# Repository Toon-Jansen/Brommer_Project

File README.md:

# Brommer Alarm
### Door Lauren Debie en Toon Jansen
Dit project bestaat uit het maken van een brommer alarm dat het achterwiel van de brommer kan blokkeren en een sirenen kan laten afgaan wanneer deze op staat. Verder zal men het alarm kunne op en afzetten met zowel de brommer sleutel al een remote keycard.

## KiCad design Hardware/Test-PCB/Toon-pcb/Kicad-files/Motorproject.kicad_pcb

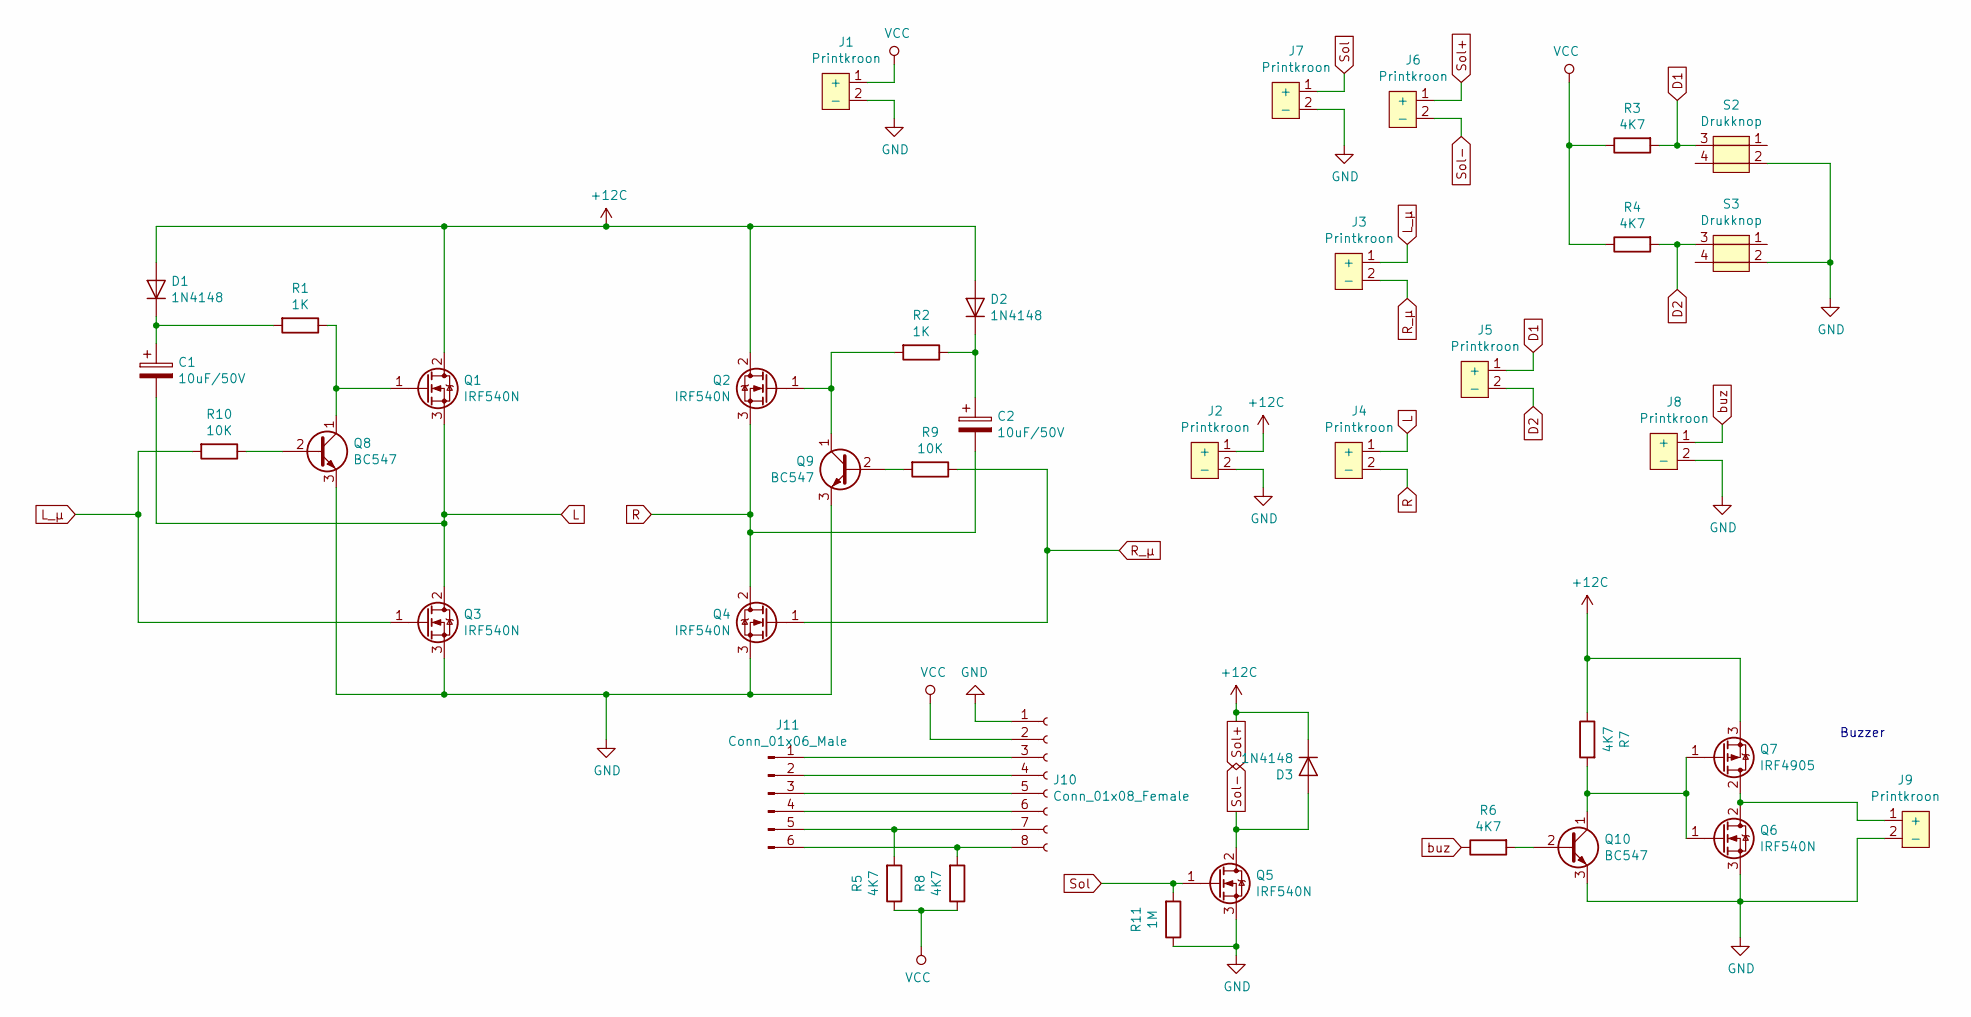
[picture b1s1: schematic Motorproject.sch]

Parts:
C1, C2: 10uF/50V; CP_EIA-6032-28_Kemet-C
D1, D2, D3: 1N4148; D_SOD-123
J1, J2, J3, J4, J5, J6, J7, J8, J9: Printkroon; SolderWirePad_1x02_P5.08mm_Drill1.5mm
J10: Conn_01x08_Female; PinHeader_1x08_P1.00mm_Vertical
J11: Conn_01x06_Male; PinHeader_1x06_P1.00mm_Vertical
Q1, Q2, Q3, Q4, Q5, Q6: IRF540N; TO-220-3_Vertical
Q7: IRF4905; TO-220-3_Vertical
Q8, Q9, Q10: BC547; TO-92_Inline
R1, R2: 1K; R_1206_3216Metric
R3, R4, R5, R6, R7, R8: 4K7; R_1206_3216Metric
R9, R10: 10K; R_1206_3216Metric
R11: 1M; R_1206_3216Metric
S2, S3: Drukknop; Drukknop_smd

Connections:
D1: J5.1 (+), R3.2, S2.3
D2: J5.2 (-), R4.2, S3.3
GND: J1.2 (-), J2.2 (-), J7.2 (-), J8.2 (-), J9.2 (-), J10.1, Q3.3 (S), Q4.3 (S), Q5.3 (S), Q6.3 (S), Q8.3 (E), Q9.3 (E), Q10.3 (E), R11.1, S2.2, S3.2
L: C1.2, J4.1 (+), Q1.3 (S), Q3.2 (D)
L_µ: J3.1 (+), Q3.1 (G), R10.2
unnamed: C1.1, D1.1 (K), R1.2
unnamed: C2.1, D2.1 (K), R2.1
unnamed: J9.1 (+), Q6.2 (D), Q7.2 (D)
unnamed: J10.3, J11.1
unnamed: J10.4, J11.2
unnamed: J10.5, J11.3
unnamed: J10.6, J11.4
unnamed: J10.7, J11.5, R5.2
unnamed: J10.8, J11.6, R8.2
unnamed: Q1.1 (G), Q8.1 (C), R1.1
unnamed: Q2.1 (G), Q9.1 (C), R2.2
unnamed: Q8.2 (B), R10.1
unnamed: Q9.2 (B), R9.2
unnamed: Q6.1 (G), Q7.1 (G), Q10.1 (C), R7.2
unnamed: Q10.2 (B), R6.2
R: C2.2, J4.2 (-), Q2.3 (S), Q4.2 (D)
R_µ: J3.2 (-), Q4.1 (G), R9.1
Sol: J7.1 (+), Q5.1 (G), R11.2
Sol+: D1.2 (A), D2.2 (A), D3.1 (K), J2.1 (+), J6.1 (+), Q1.2 (D), Q2.2 (D), Q7.3 (S), R7.1
Sol-: D3.2 (A), J6.2 (-), Q5.2 (D)
VCC: J1.1 (+), J10.2, R3.1, R4.1, R5.1, R8.1
buz: J8.1 (+), R6.1

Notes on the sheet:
Buzzer

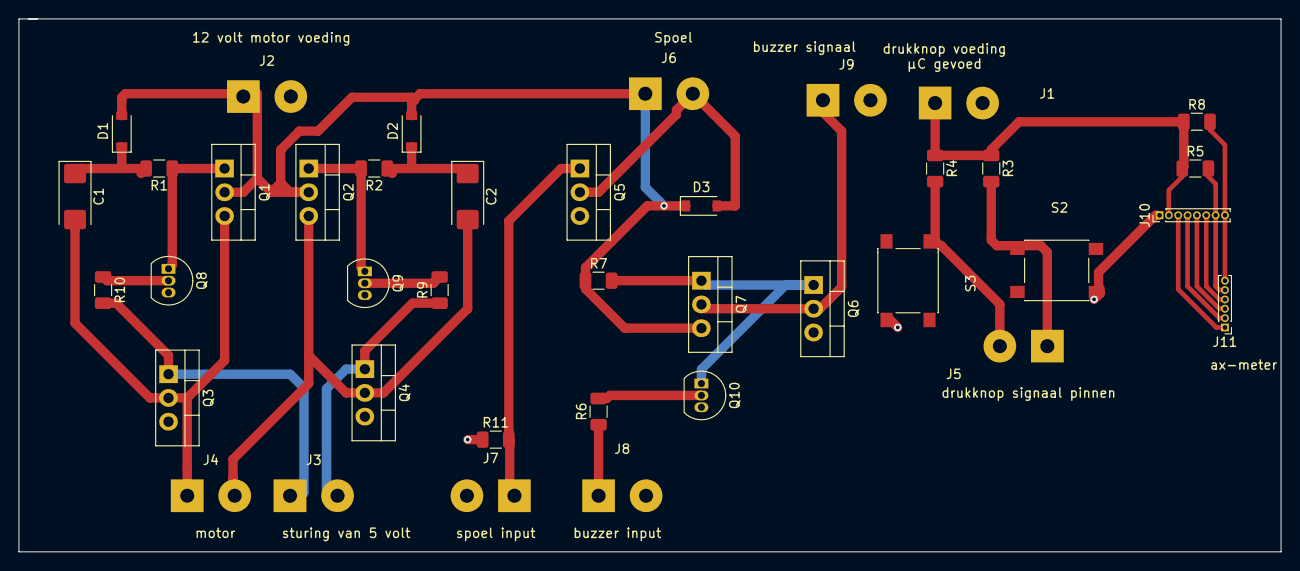
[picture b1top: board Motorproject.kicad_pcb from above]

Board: 2 copper layers, 135.0 x 57.0 mm, 39 parts (0 on the bottom side), 27 nets.

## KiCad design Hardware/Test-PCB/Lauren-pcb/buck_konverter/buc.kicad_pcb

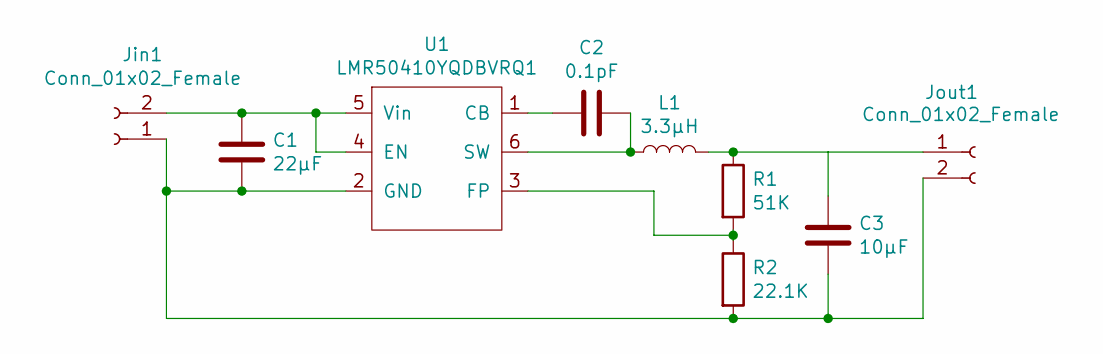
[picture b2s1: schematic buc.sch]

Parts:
C1: 22µF; C_0805_2012Metric
C2: 0.1pF; C_0805_2012Metric
C3: 10µF; C_0805_2012Metric
Jin1: Conn_01x02_Female; PinHeader_1x02_P2.54mm_Vertical
Jout1: Conn_01x02_Female; PinHeader_1x02_P2.54mm_Vertical
L1: 3.3µH; L_Taiyo-Yuden_MD-1616
R1: 51K; R_0603_1608Metric_Pad1.05x0.95mm_HandSolder
R2: 22.1K; R_0603_1608Metric_Pad1.05x0.95mm_HandSolder
U1: LMR50410YQDBVRQ1; SOT-23-6

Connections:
unnamed: C1.1, Jin1.2, U1.4 (EN), U1.5 (Vin)
unnamed: C1.2, C3.2, Jin1.1, Jout1.2, R2.2, U1.2 (GND)
unnamed: C2.1, U1.1 (CB)
unnamed: C2.2, L1.1, U1.6 (SW)
unnamed: C3.1, Jout1.1, L1.2, R1.1
unnamed: R1.2, R2.1, U1.3 (FP)

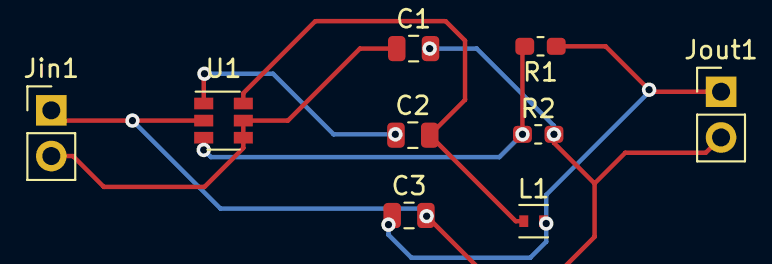
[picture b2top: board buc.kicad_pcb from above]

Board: 2 copper layers, 9 parts (0 on the bottom side), 6 nets.

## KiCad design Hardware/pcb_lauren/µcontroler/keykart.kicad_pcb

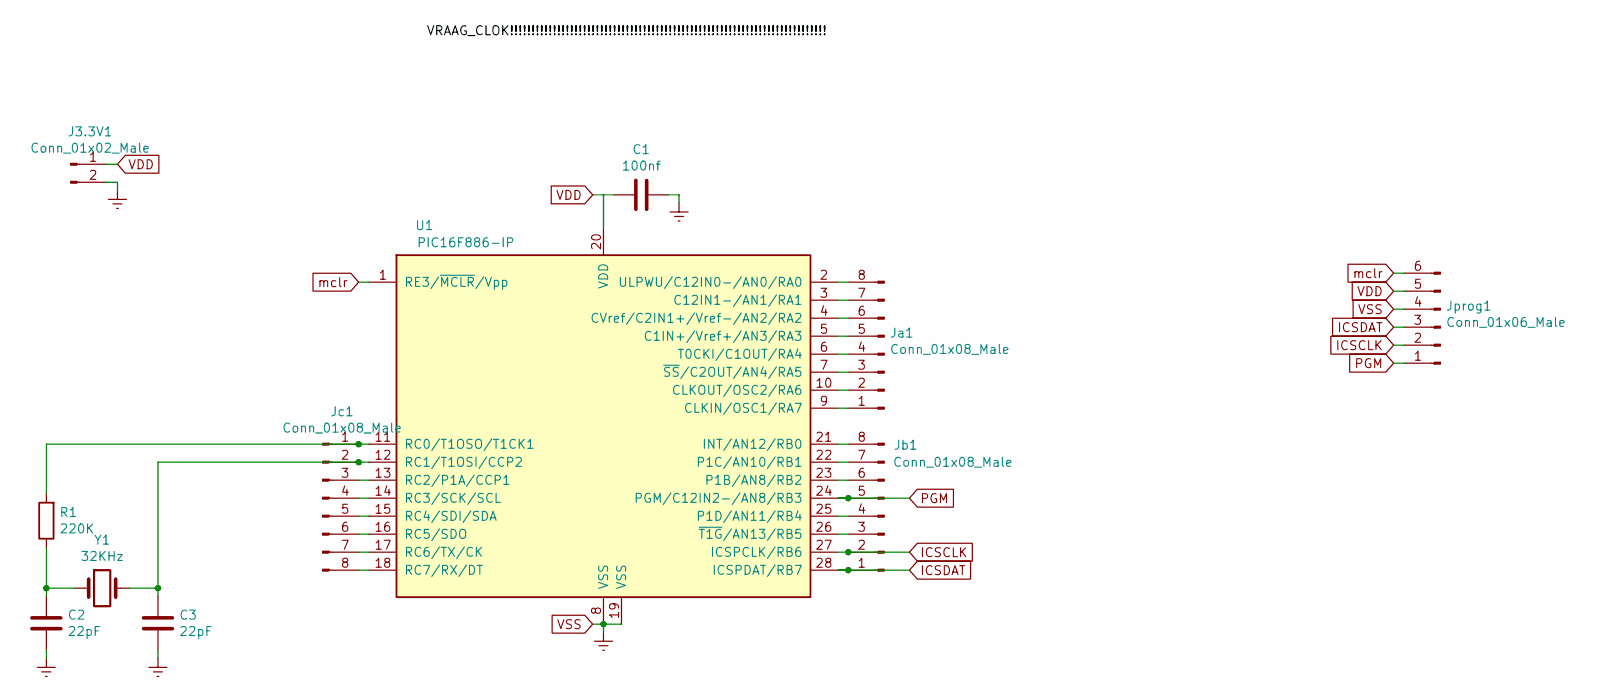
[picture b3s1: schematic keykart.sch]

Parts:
C1: 100nf; C_1210_3225Metric
C2, C3: 22pF; C_1812_4532Metric
J3.3V1: Conn_01x02_Male; PinHeader_1x02_P2.54mm_Vertical
Ja1: Conn_01x08_Male; PinHeader_1x08_P2.54mm_Vertical
Jb1: Conn_01x08_Male; PinHeader_1x08_P2.54mm_Vertical
Jc1: Conn_01x08_Male; PinHeader_1x08_P2.54mm_Vertical
Jprog1: Conn_01x06_Male; PinHeader_1x06_P2.54mm_Vertical
R1: 220K; R_0603_1608Metric_Pad1.05x0.95mm_HandSolder
U1: PIC16F886-IP; SSOP-28_5.3x10.2mm_P0.65mm
Y1: 32KHz; Crystal_DS26_D2.0mm_L6.0mm_Horizontal_1EP_style1

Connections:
ICSCLK: Jb1.2, Jprog1.2, U1.27 (ICSPCLK/RB6)
ICSDAT: Jb1.1, Jprog1.3, U1.28 (ICSPDAT/RB7)
unnamed: C2.2, R1.1, Y1.1
unnamed: C3.2, Jc1.2, U1.12 (RC1/T1OSI/CCP2), Y1.2
unnamed: Ja1.1, U1.9 (CLKIN/OSC1/RA7)
unnamed: Ja1.2, U1.10 (CLKOUT/OSC2/RA6)
unnamed: Ja1.3, U1.7 (~SS~/C2OUT/AN4/RA5)
unnamed: Ja1.4, U1.6 (T0CKI/C1OUT/RA4)
unnamed: Ja1.5, U1.5 (C1IN+/Vref+/AN3/RA3)
unnamed: Ja1.6, U1.4 (CVref/C2IN1+/Vref-/AN2/RA2)
unnamed: Ja1.7, U1.3 (C12IN1-/AN1/RA1)
unnamed: Ja1.8, U1.2 (ULPWU/C12IN0-/AN0/RA0)
unnamed: Jb1.3, U1.26 (~T1G~/AN13/RB5)
unnamed: Jb1.4, U1.25 (P1D/AN11/RB4)
unnamed: Jb1.6, U1.23 (P1B/AN8/RB2)
unnamed: Jb1.7, U1.22 (P1C/AN10/RB1)
unnamed: Jb1.8, U1.21 (INT/AN12/RB0)
unnamed: Jc1.1, R1.2, U1.11 (RC0/T1OSO/T1CK1)
unnamed: Jc1.3, U1.13 (RC2/P1A/CCP1)
unnamed: Jc1.4, U1.14 (RC3/SCK/SCL)
unnamed: Jc1.5, U1.15 (RC4/SDI/SDA)
unnamed: Jc1.6, U1.16 (RC5/SDO)
unnamed: Jc1.7, U1.17 (RC6/TX/CK)
unnamed: Jc1.8, U1.18 (RC7/RX/DT)
PGM: Jb1.5, Jprog1.1, U1.24 (PGM/C12IN2-/AN8/RB3)
VDD: C1.1, J3.3V1.1, Jprog1.5, U1.20 (VDD)
VSS: C1.2, C2.1, C3.1, J3.3V1.2, Jprog1.4, U1.8 (VSS), U1.19 (VSS)
mclr: Jprog1.6, U1.1 (RE3/~MCLR~/Vpp)

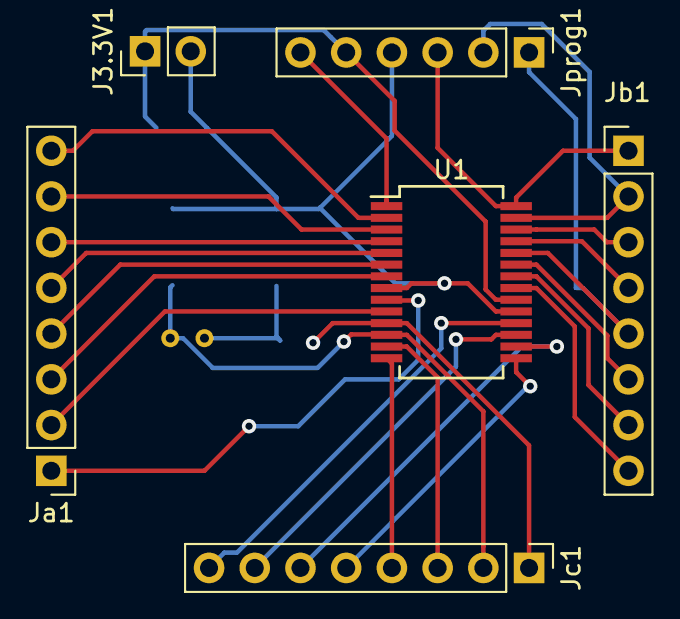
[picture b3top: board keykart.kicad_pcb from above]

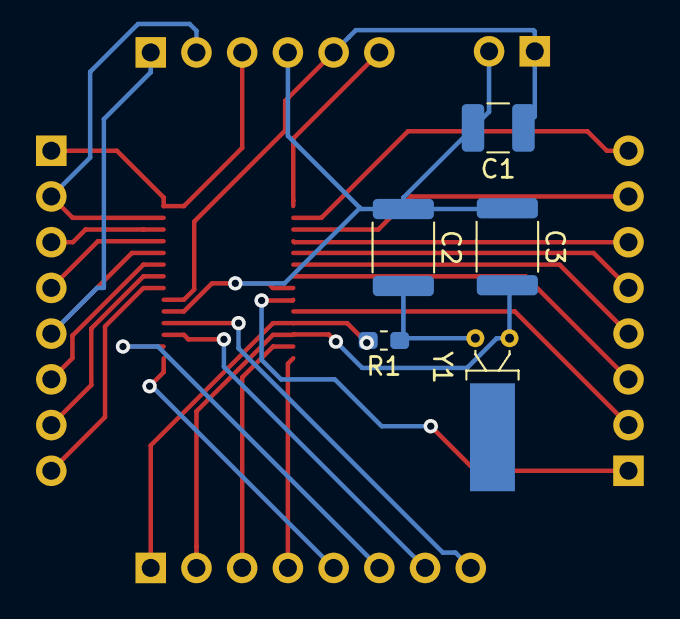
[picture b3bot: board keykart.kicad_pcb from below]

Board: 2 copper layers, 11 parts (5 on the bottom side), 28 nets.

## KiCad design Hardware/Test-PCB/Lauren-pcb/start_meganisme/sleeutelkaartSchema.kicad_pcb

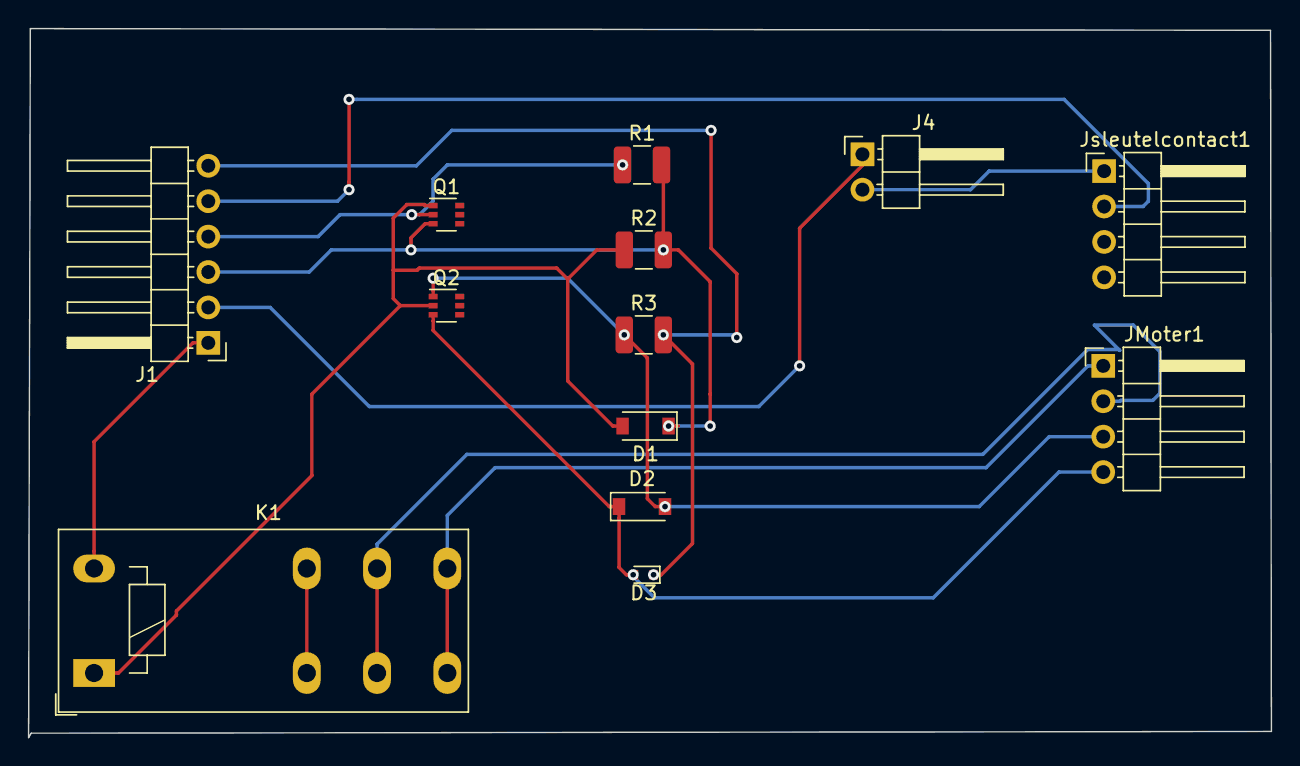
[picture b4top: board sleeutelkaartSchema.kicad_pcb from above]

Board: 2 copper layers, 89.2 x 50.9 mm, 13 parts (0 on the bottom side), 12 nets.

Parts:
D1, D2: DIODE; D_SOD-123
D3: D_Zener_3V; D_SOD-523
J1: Conn_01x06_Male; PinHeader_1x06_P2.54mm_Horizontal
J4: Conn_01x02_Female; PinHeader_1x02_P2.54mm_Horizontal
JMoter1: Conn_01x04_Female; PinHeader_1x04_P2.54mm_Horizontal
Jsleutelcontact1: Conn_01x04_Female; PinHeader_1x04_P2.54mm_Horizontal
K1: DIPxx-1Cxx-51x; Relay_SPDT_Schrack-RT1-16A-FormC_RM5mm
Q1, Q2: Q_NMOS_DGS; SOT-363_SC-70-6
R1, R2, R3: 1M; R_1210_3225Metric

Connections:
3.3v: J1.2, J4.1
12V: J1.1, K1.6
Earth: D1.1, J1.3, Q1.3, R1.2, R2.2
Motor-On: D3.1, J1.6, R3.2
unnamed: D1.2, K1.2, Q1.1, Q2.2, R2.1
unnamed: J4.2, Jsleutelcontact1.1
Sleutelcontact-: J1.5, Jsleutelcontact1.2
kill+: D2.2, JMoter1.3, Q2.1, R3.1
kill-: D2.1, D3.2, JMoter1.4, Q2.3
moter_ON_OFF: J1.4, Q1.2, R1.1
motor+: JMoter1.1, K1.14
motor-: JMoter1.2, K1.7

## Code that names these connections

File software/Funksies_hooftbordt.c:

#include <xc.h>
#include <pic16f886.h>

#include "hooftcode/header/FUNKSIES_heade.h"

#define _XTAL_FREQ 1000000


//inisialisatsie////////////////////////////////////////////////////////////////
void init_Alarmboard(void)
{
    // zet klok
    init_clk(2);
    //druknoppern
    TRISA1 = 1; //zet input (is slot knop)
    TRISA2 = 1; //zet input
    TRISA0 = 1; //zet input

    ANS1 = 0; // zet op digital input
    ANS2 = 0; // zet op digital input
    ANS0 = 0; // zet op digital input
    //solinoide
    TRISB2 = 0; //zet als output
    
    //bromer moterr meganisme
    TRISC5 = 1; //zet input
    TRISC2 = 0; //zet output    
    
    //hbrug
    
    
    TRISA3 = 0; //zet output
    TRISA4 = 0; //zet output
    
    I2C_Initialize(2500);
    config_Ac();
    init_alarm();
}
////////////////////////////////////////////////////////////////////////////////

//kijken of de brommer beweegt /////////////////////////////////////////////////
int beweeg(void){
    int detect = 0;
    unsigned int waarde[5] = {0,0,0,0,0};
    unsigned int hoog = 0,buf = 0,laag = 0;
    for(int i = 0; i < 5; i++)
    {
        waarde[i] = lees();
        __delay_ms(1000);
    }
    hoog = waarde[0];
    laag = waarde[1];
    if(hoog < laag){
        buf = hoog;
        hoog = laag;
        laag = buf;
    }
    for(int i = 0; i < 5; i++)
    {
        if(waarde[i] < laag)
        {
            laag = waarde[i];
        }
        if(waarde[i] > hoog){
            hoog = waarde[i];
        }
    }
    buf = hoog - laag;
    if(buf > 800)
    {
        detect =1;
    }
    return detect;
}
////////////////////////////////////////////////////////////////////////////////
//kijk of keykart in de buurt is////////////////////////////////////////////////
int keykard(void)
{
    //moet "1" stuuren waneer inbeweging en een "0" waaneer stilstaat
    __delay_ms(4000);
    // debie das aan u
    return RA2;
}
////////////////////////////////////////////////////////////////////////////////

//zet slot op //////////////////////////////////////////////////////////////////
void SLOT_op(void)
{
     RC2 = 0;
     TRISB = 0;
    RB2 = 1;
    __delay_ms(500);
    while(RA1 == 0)
    {
        PORTA = PORTA | 0b00010000;
        __delay_us(300);
        
        __delay_us(600);
        PORTA = PORTA & 0b11101111;
    }
    __delay_ms(500);
    TRISB = 0;
    PORTB = 0;
}
////////////////////////////////////////////////////////////////////////////////

//zet slot af //////////////////////////////////////////////////////////////////
void SLOT_aff(void)
{
    RC2 = 1;
       PORTB = 0b000000100;
    __delay_ms(500);
    while(RA1 == 1)
    {
         PORTA = PORTA | 0b00001000;
        __delay_us(300);
        PORTA = PORTA & 0b11110111;
        __delay_us(600); 
    }
    __delay_ms(500);
    PORTB = 0;
    
}
////////////////////////////////////////////////////////////////////////////////

//alarm/////////////////////////////////////////////////////////////////////////
void init_alarm(void){
    TRISB4 = 0;
    TRISB5 = 0;
    RB4 = 0;
    RB5 = 0;
}
////////////////////////////////////////////////////////////////////////////////
void alarm(int s){
    RB4 = 0;
    RB5 = 0;
    if(s == 1){
        for(short j = 0; j < 3; j++){
            for(short i = 301; i>0; i--){
                RB5 = 0;
                __delay_us(1);
                RB4 = 1;
                __delay_us(249);
                RB4 = 0;
                __delay_us(1);
                RB5 = 1;
                __delay_us(249);
                RB5 = 0;
            }
            __delay_ms(175);
        }
    }
    if(s == 2){
        for(short j = 0; j < 3; j++){
            for(short i = 1101; i>0; i--){
                RB5 = 0;
                __delay_us(1);
                RB4 = 1;
                __delay_us(249);
                RB4 = 0;
                __delay_us(1);
                RB5 = 1;
                __delay_us(249);
                RB5 = 0;
            }
            __delay_ms(550);
        }
    }
}
////////////////////////////////////////////////////////////////////////////////
////////////////////////////////////////////////////////////////////////////////
////////////////////////////////////////////////////////////////////////////////
////////////////////////////////////////////////////////////////////////////////
void I2C_Initialize(const unsigned long feq_K) //Begin I2C com als Master
{
  TRISC3 = 1;  TRISC4 = 1;  //Maak RC3 en RC4, SDA en SCL, input pins
  TRISC0 = 1; //interrupt pin 

  SSPCON  = 0b00101000;    //enable serial port en gebruik SDA & SCL
                           //master mode speed = FOSC/(4*(SSPADD+1))
  SSPCON2 = 0b00000000;    //Idle mode aanzetten 

  SSPADD = (_XTAL_FREQ/(4*feq_K*100))-1; //user bepaalde snelheid van I2C bus
  SSPSTAT = 0b00000000;    //Info van de bus leegmaken
}
void I2C_Hold()
{
    while (   (SSPCON2 & 0b00011111)    ||    (SSPSTAT & 0b00000100)   ) ; 
                           //check dat de I2C bus niet langer in gebruik is
}
void I2C_Begin()
{
  I2C_Hold();  //Wacht tot bus beschikbaar is
  SEN = 1;     //Stuur start conditie
}
void I2C_End()
{
  I2C_Hold(); //Wacht tot bus beschikbaar is
  PEN = 1;    //Stuur stop conditie
}
void I2C_Write(unsigned data)
{
  I2C_Hold(); //Wacht tot bus beschikbaar is
  SSPBUF = data;         //stuur data in buffer op I2C bus
}
unsigned short I2C_Read(unsigned short ack)
{
  unsigned short incoming; //var voor aangekregen data
  I2C_Hold(); //Wacht tot bus beschikbaar is
  RCEN = 1;   //Klaar zetten voor data te ontvangen

  I2C_Hold(); //Wacht tot bus beschikbaar is
  incoming = SSPBUF;      //zet aangekregen data van buffer naar var

  I2C_Hold(); //Wacht tot bus beschikbaar is
  ACKDT = (ack)?0:1;    //check if ack bit received 
  ACKEN = 1;          //lees Ack bit in

  return incoming; //stuur aagekregen data terug
}
void config_Ac(void){
    I2C_Begin();
    I2C_Write(0xD0); //Schrijf adres van accel (68+R/not(W))
    I2C_Write(0x6B); //power mngmt 1
    I2C_Write(0x80); //Voer reset uit
    I2C_End();
    __delay_ms(100);
    I2C_Begin();
    I2C_Write(0xD0);
    I2C_Write(0x68); //sig reset register
    I2C_Write(0x07); //reset meters
    I2C_End();
    __delay_ms(100);
    I2C_Begin();
    I2C_Write(0xD0);
    I2C_Write(0x6B); //open power mngmt 1 opnieuw
    I2C_Write(0x2D); //zet lowpowermode aan en gebruikt ext 19.2MHz
    I2C_Write(0x47); //(schrijft door naar 6C) 5Hz wake up cycle en gyro standby
    I2C_End();
    I2C_Begin();
    I2C_Write(0xD0);
    I2C_Write(0xB7); //interrupt config register
    I2C_Write(0x30); //zorg dat interrupt pin hoog blijft tot ik reg lees
    I2C_Write(0x01); //genereer int als data klaar staat
    I2C_End();
    I2C_Begin();
    I2C_Write(0xD0);
    I2C_Write(0x1C); //configure accelerometer
    I2C_Write(0x00); //selecteer scale van +-16g
    I2C_End();
}
unsigned int lees(void){
    signed char I2C_DH = 0; //var voor de ontvangen data in High reg
    unsigned char I2C_DL = 0; //var voor de ontvangen data in Low reg
    unsigned int rek = 0;
    unsigned char ref = 0xff;
    unsigned int tot = 0;//var voor de totale waarde van accel
    I2C_Begin();
    I2C_Write(0xD0);
    I2C_Write(0x3D);
    I2C_Begin();
    I2C_Write(0xD1);
    I2C_DH = I2C_Read(1);
    I2C_DL = I2C_Read(0);
    I2C_End();
    for(int i = 0; i < 4; i++){
        //while(RC0 == 1); //wacht tot data klaar staat om gelezen te worden
        I2C_Begin();
        I2C_Write(0xD0);
        I2C_Write(0x3D);
        I2C_Begin();
        I2C_Write(0xD1);
        I2C_DH = I2C_Read(1);
        I2C_DL = I2C_Read(0);
        I2C_End();
        if(I2C_DH < 0){
            I2C_DH = ref - I2C_DH;
            I2C_DH += 1;
        }
        rek = I2C_DH;
        rek = rek<<8;
        rek = rek | I2C_DL;
        rek = rek>>2;
        tot += rek;
        rek = 0;
    }
    return tot;
    }
////////////////////////////////////////////////////////////////////////////////

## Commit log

2021-03-08 aanpassing algemene beschrijving
2021-03-08 create hardware description
2021-03-08 aanmaken beschrijving
2021-03-08 beschrijving README file
2021-03-08 Update Hardware Readme file
2021-03-08 Update readme file
2021-03-08 uploding pcbs lauren
2021-03-13 Add kicad files testbord in hardware
2021-03-13 document hiërarchie update
2021-03-16 make furst project
2021-05-06 Create FUNKSIES.h
    eerste uplowd Lauren
2021-05-06 start files
2021-05-06 backbone
2021-05-08 making things ride
2021-05-08 testing things
2021-05-08 just testing
2021-05-08 just bizie whit testing
2021-05-08 i thingk i got it
2021-05-08 ja der moet getest worden he
2021-05-08 invoegen dat interne klok ook op 1Mhz kan gezet worden
2021-05-08 Spelling controleren
2021-05-08 verwijder
2021-05-08 I2C werking test
2021-05-09 making uart
2021-05-10 toon ik zen u friste verschuldig ik had een fout gemaakt bij klok init ma die is nu opgelost
2021-05-10 het werkt!!!!!!!!
2021-05-10 hier moet ik u ook fristie voor ma normaal moet het trug normaal werken anders stuurt ma een boos bericht naar mij
2021-05-13 may god rfmodulles kunne comuniceeren
2021-05-13 just plying
2021-05-13 template bundel
2021-05-14 ligge kutte
2021-05-14 I2C communicatie met Accel
2021-05-15 Accel aan de praat krijgen
2021-05-15 Accel waarde lezen
2021-05-16 making kode keykart
2021-05-16 maaken keykart main
2021-05-16 making a functie
2021-05-16 Werkende I2C resultaten + functie
2021-05-18 Buzzer + I2C lees functies
2021-05-20 teste
2021-05-20 Auteur's bewerken en spelling
2021-05-21 Bewerking verslag
2021-05-21 aanpassingen verslag
2021-05-21 Volledige versie bundel (zonder code)
2021-05-21 Woordje vergeten T_T
2021-05-21 Opmerking van Mr. Verholen weg
2021-05-21 Iedere afbeelding fig.xx T-T
2021-05-21 making test kode hooft project
2021-05-23 complete bewegingsdetectie
2021-05-24 aanpasingen
2021-05-24 inhoop van fukking zege
2021-05-24 fukking kut uar
2021-05-24 def code afmaken
2021-05-24 aanpassingen final code
2021-05-24 probleem
2021-05-24 lieve hemel god gehijligt zijt uw naam het fukking werkt!!!!!!!!!!!!!!!!!!!!!!!!!!!!!!!!!!!!!!!!!!!!!!!!!!!!!!
    manne ik denk dak zwanger zijn
2021-05-24 dit is wa properder
